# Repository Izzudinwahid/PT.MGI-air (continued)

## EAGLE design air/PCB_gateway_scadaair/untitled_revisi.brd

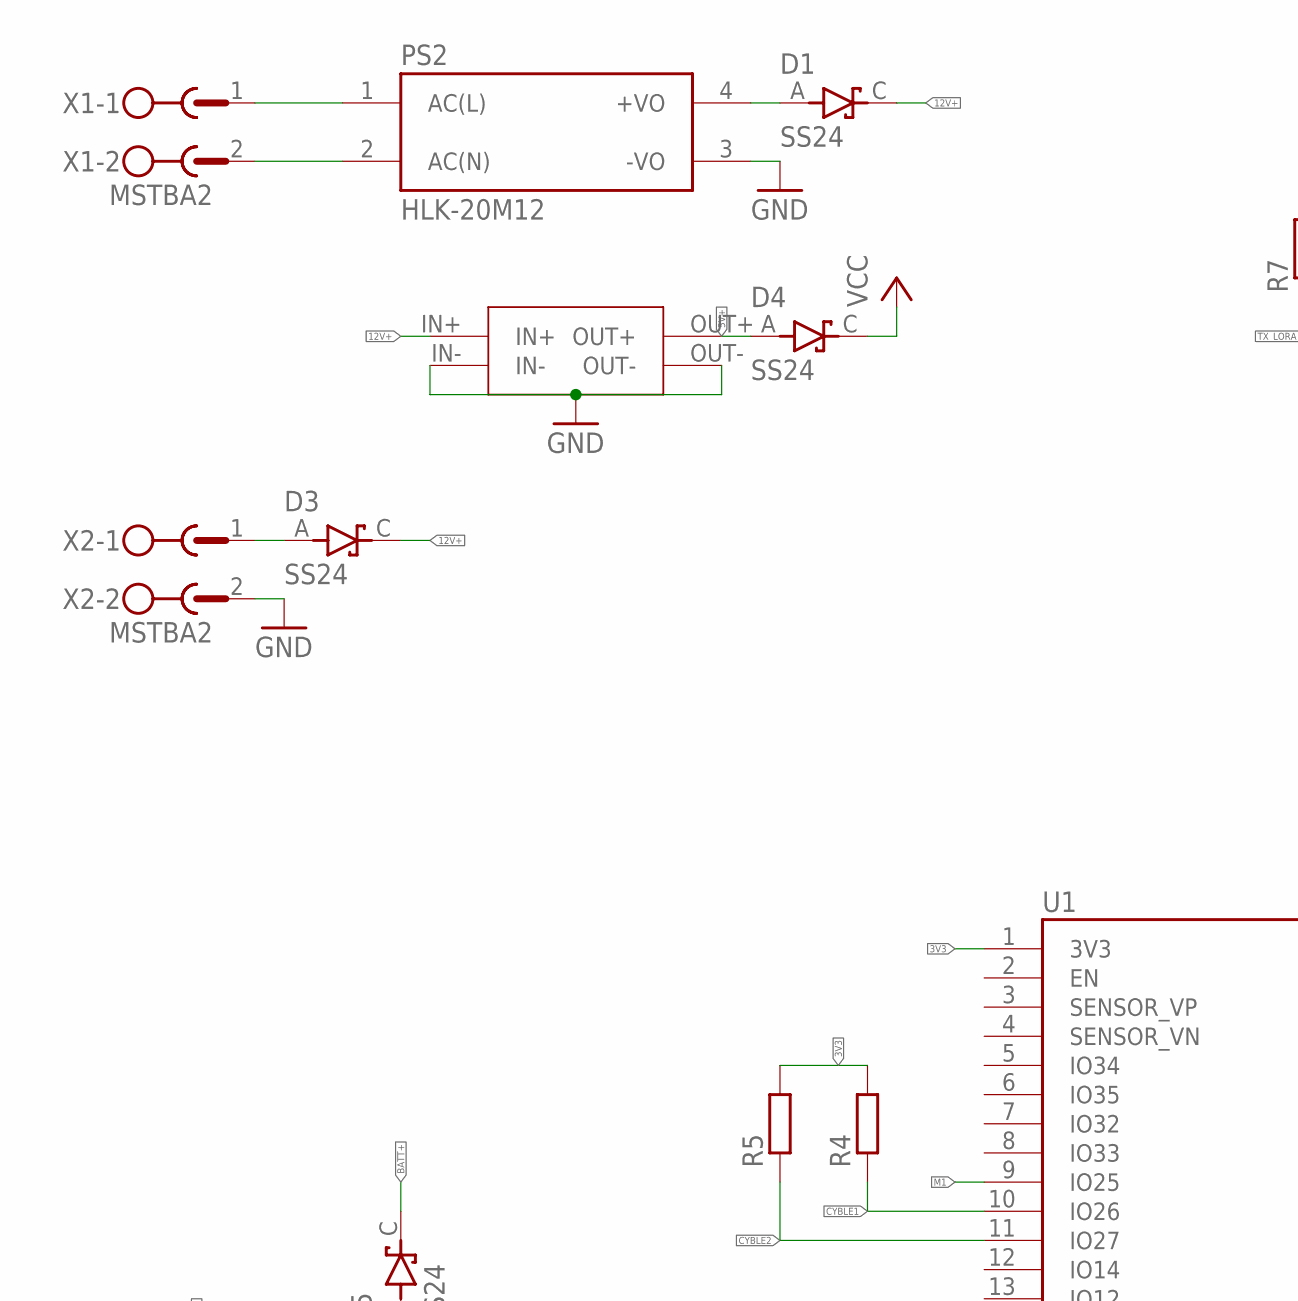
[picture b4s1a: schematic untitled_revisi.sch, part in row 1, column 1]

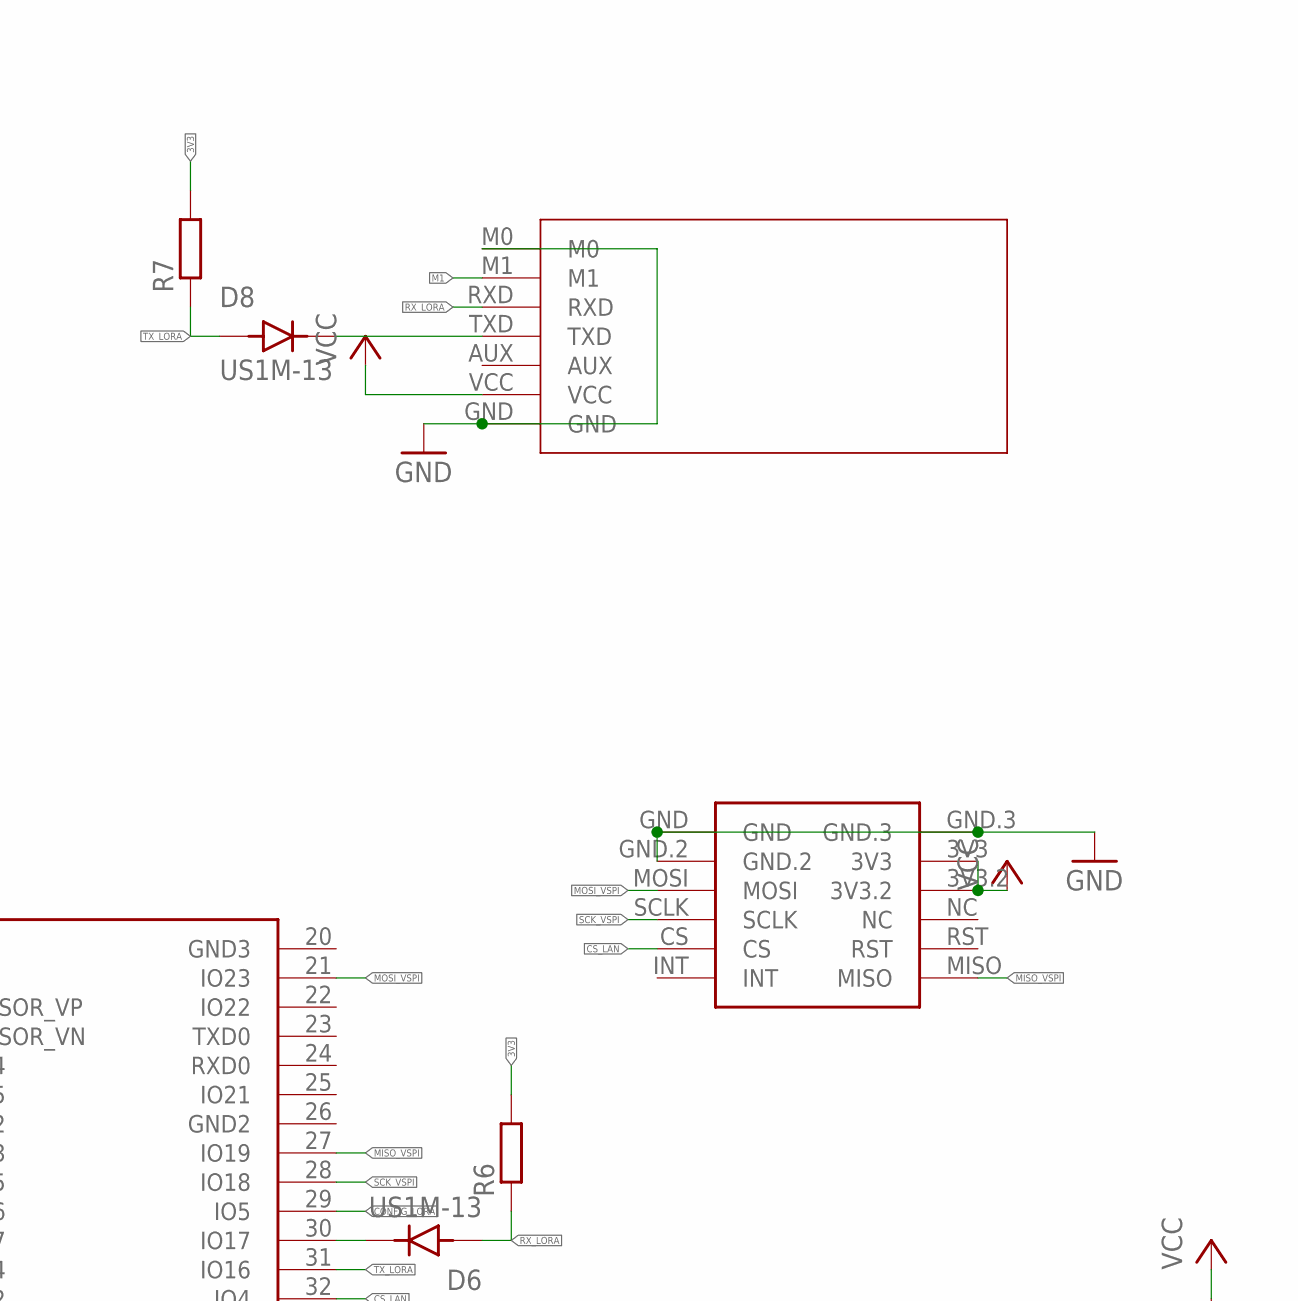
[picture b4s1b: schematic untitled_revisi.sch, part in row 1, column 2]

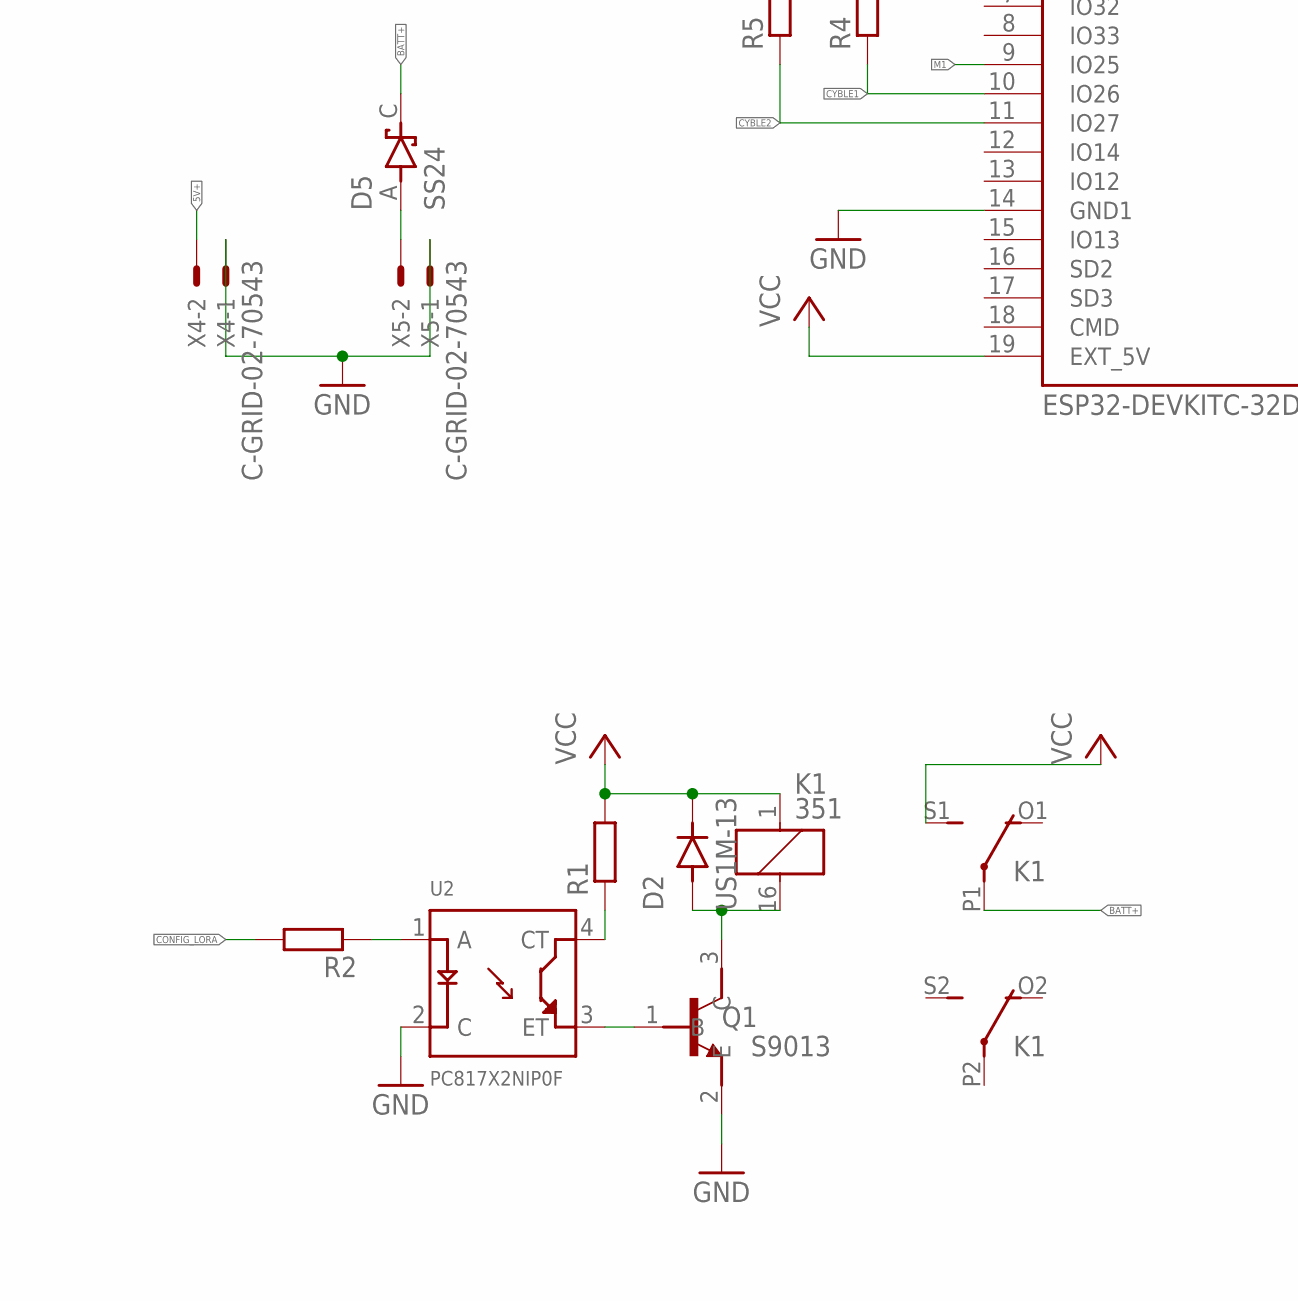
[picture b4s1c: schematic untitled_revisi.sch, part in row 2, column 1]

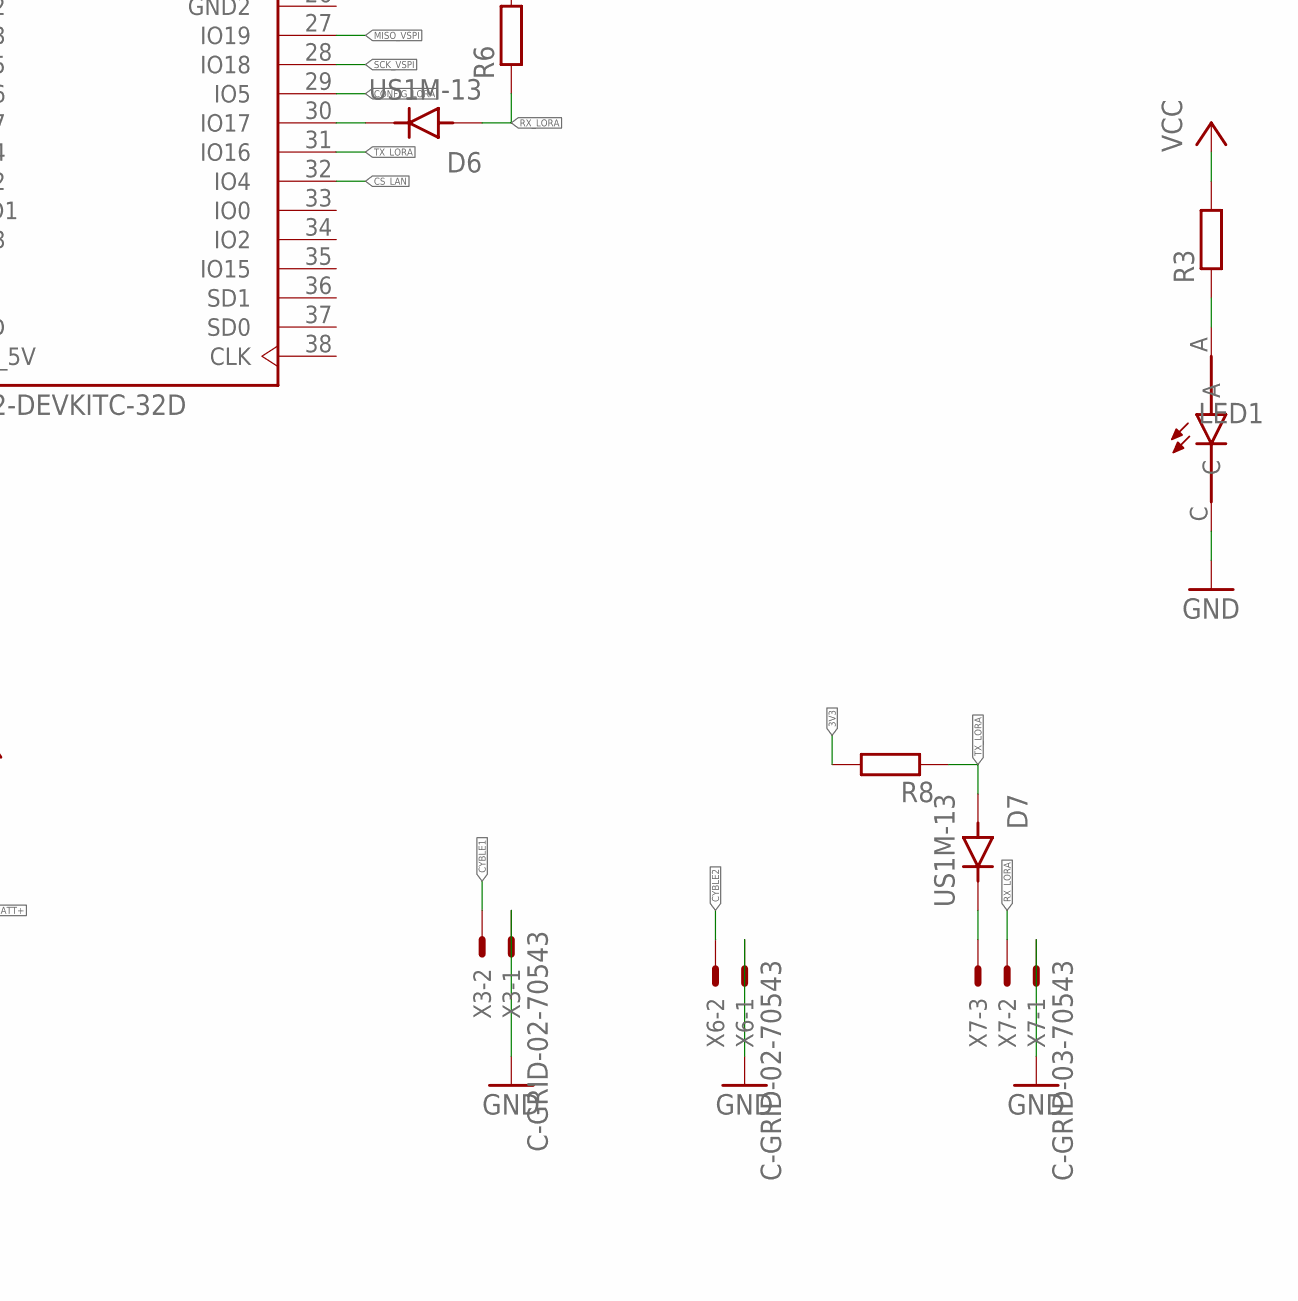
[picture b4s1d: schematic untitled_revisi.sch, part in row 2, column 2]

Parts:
D1, D3, D4, D5: SS24; DIOM5336X265N
D2, D6, D7, D8: US1M-13; DIOM5226X240N
EBYTEE220-900T22D1: EBYTEE220-900T22D
K1: 351
LED1: SML-LXT0805IW-TR; LEDC2012X120N
MINI1: MINI560
PS2: HLK-20M12; CONV_HLK-20M12
Q1: S9013; SOT95P240X120-3N
R1, R2, R3, R4, R5, R6, R7, R8: R-EU_R0805; R0805
U1: ESP32-DEVKITC-32D; MODULE_ESP32-DEVKITC-32D
U2: PC817X2NIP0F; SOT254P975X400-4N
U$1: MINI_W5500
X1, X2: MSTBA2
X3, X4, X5, X6: C-GRID-02-70543; 70543-02
X7: C-GRID-03-70543; 70543-03

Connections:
3V3: R4.2, R5.2, R6.2, R7.2, R8.2, U1.1 (3V3)
5V+: D4.A, MINI1.OUT+, X4.2
12V+: D1.C (K), D3.C (K), MINI1.IN+
BATT+: D5.C (K), K1.P1
CONFIG_LORA: R2.2, U1.29 (IO5)
CS_LAN: U1.32 (IO4), U$1.CS
CYBLE1: R4.1, U1.10 (IO26), X3.2
CYBLE2: R5.1, U1.11 (IO27), X6.2
GND: EBYTEE220-900T22D1.GND, EBYTEE220-900T22D1.M0, LED1.C, MINI1.IN-, MINI1.OUT-, PS2.3 (-VO), Q1.2 (E), U1.14 (GND1), U2.2 (C), U$1.GND, U$1.GND.2, U$1.GND.3, X2.2, X3.1, X4.1, X5.1, X6.1, X7.1
GND2: U1.26 (GND2)
GND3: U1.20 (GND3)
M1: EBYTEE220-900T22D1.M1, U1.9 (IO25)
MISO_VSPI: U1.27 (IO19), U$1.MISO
MOSI_VSPI: U1.21 (IO23), U$1.MOSI
unnamed: PS2.1 (AC(L)), X1.1
unnamed: PS2.2 (AC(N)), X1.2
unnamed: D1.A, PS2.4 (+VO)
unnamed: R2.1, U2.1 (A)
unnamed: D3.A, X2.1
unnamed: D2.A, K1.16 (2), Q1.3 (C)
unnamed: Q1.1 (B), U2.3 (ET)
unnamed: R1.1, U2.4 (CT)
unnamed: D6.C (K), U1.30 (IO17)
unnamed: LED1.A, R3.1
unnamed: D8.C (K), EBYTEE220-900T22D1.TXD
unnamed: D5.A, X5.2
unnamed: D7.C (K), X7.3
RX_LORA: D6.A, EBYTEE220-900T22D1.RXD, R6.1, X7.2
SCK_VSPI: U1.28 (IO18), U$1.SCLK
TX_LORA: D7.A, D8.A, R7.1, R8.1, U1.31 (IO16)
VCC: D2.C (K), D4.C (K), EBYTEE220-900T22D1.VCC, K1.1, K1.S1 (S), R1.2, R3.2, U1.19 (EXT_5V), U$1.3V3, U$1.3V3.2

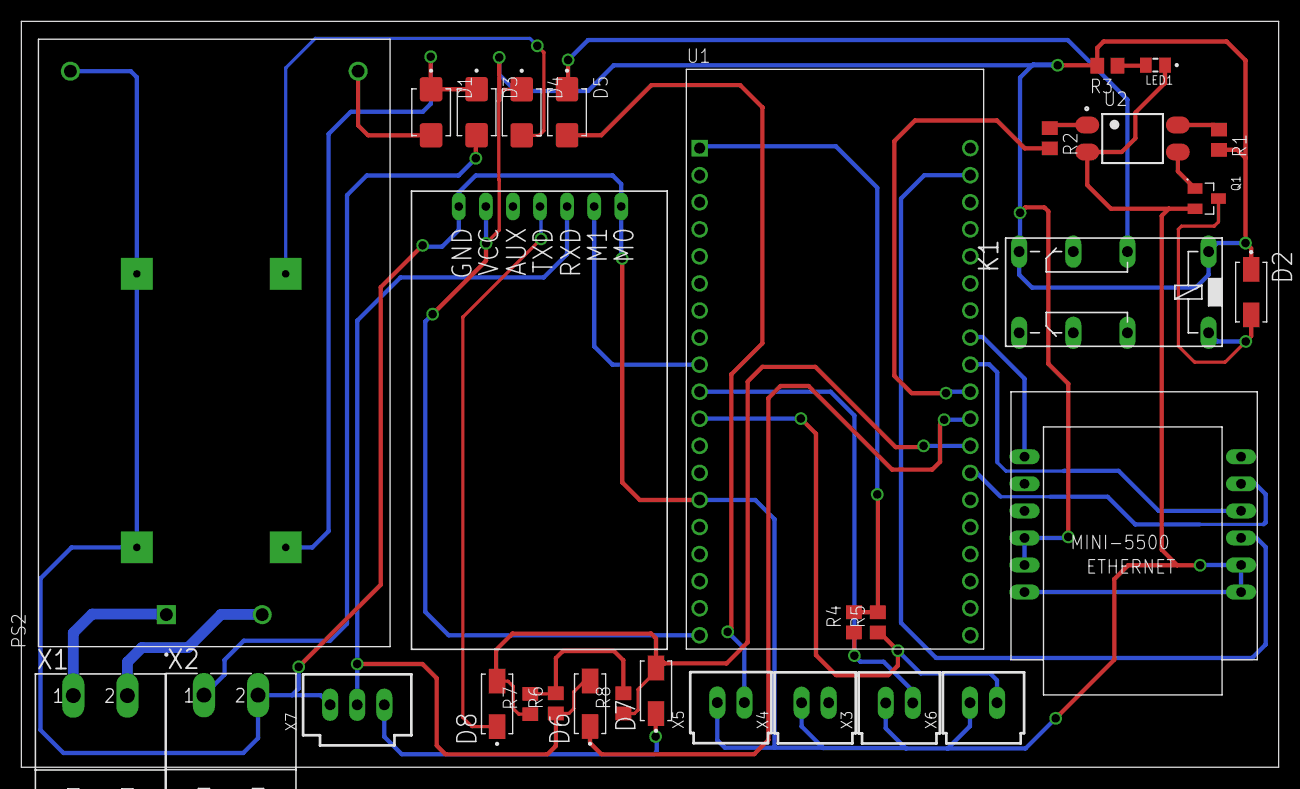
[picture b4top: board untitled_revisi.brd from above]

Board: 2 copper layers, 118.0 x 70.0 mm, 32 parts (1 on the bottom side), 29 nets.

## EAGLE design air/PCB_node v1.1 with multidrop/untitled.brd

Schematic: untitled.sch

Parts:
ADS1, ADS2: ADS1115
BT1: ML414H_IV01E; SEIKO_ML414H_IV01E
C1, C7, C8, C9, C14, C19, C20, C24: 1uF; C0805K
C2, C6, C15: 10uF/16V; 153CLV-0505
C3, C10, C11, C16, C17, C18, C21: 100nF; C0805K
C4, C5, C12, C13: 22pF; C0805K
C22: 27nH; C0805K
C23: 10nF; C0805K
D1, D2, D7, D8, D17: 1N5819HW-7; SOD3715X145N
D3, D9, D10, D11, D12, D16: SML-LXT0805IW-TR; LEDC2012X120N
D4, D5, D6, D13, D14, D15, D18: US1M-13; DIOM5226X240N
EBYTEE220-900T22D1: EBYTEE220-900T22D
J1, J2: 10118193-0001LF; FCI_10118193-0001LF
J3: U.FL-R-SMT(01); HRS_U.FL-R-SMT(01)
K1, K2, K4, K5: 351
K3: SRD-05VDC-SL-C; RELAY_SRD-05VDC-SL-C
NEO-6MGPS1: NEO-6MGPS
Q1, Q2, Q8, Q9: MMBT3904; SOT95P240X120-3N
Q3, Q7: 12MHz; SM49
Q4, Q5, Q6, Q10, Q11, Q12: S9013; SOT95P240X120-3N
R1, R2, R4, R5, R12, R14, R17, R18, R19, R20, R24, R25, R26, R27, R28, R29, R31, R35, R37: 10k; M0805
R3, R11, R13, R22, R23, R33, R34, R36: 1k; M0805
R6, R7, R8, R10, R30: 560; M0805
R9, R15, R16, R21: R-EU_0207/12; 0207/12
R32: 10; M0805
S1, S2, S3, S4: TL1015AF160QG; SW_TL1015AF160QG
SJ1, SJ2, SJ3: SJ
SUPER-STEPDOWN1: SUPER-STEPDOWN
SV1: FE09-1; FE09
U1, U7: CH340G; SOIC127P600X180-16N
U2, U9: ESP32-WROOM-32D; MODULE_ESP32-WROOM-32D
U3, U8: AMS1117; SOT229P700X180-4N
U4, U5, U6, U11, U13: PC817X2NIP0F; SOT254P975X400-4N
U10: ADS1115IDGSR; SOP50P490X110-10N
U12: NEO-M8N-0; XCVR_NEO-M8N-0
X1, X2, X5, X8: MSTBA2
X3, X6: MSTBA4
X4: MSTBA3
X7: C-GRID-02-70543; 70543-02

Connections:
24V+: R15.2, SUPER-STEPDOWN1.IN+, X1.1
A0: ADS1.A0, ADS2.A0, R15.1, R16.2, U10.4 (AIN0)
A1: ADS1.A1
A2: ADS1.A2
A3: ADS1.A3
BACKUP: BT1.1 (POS), C24.1, R34.1, U12.22 (V_BCKP)
CONFIG_LORA: R11.2, U9.10 (IO25)
CYBLE1: R6.1, U2.10 (IO25), X3.1
CYBLE2: R7.1, U2.11 (IO26), X3.2
CYBLE3: R8.1, R9.1, R21.2, U2.12 (IO27)
CYBLE4: R23.2, U2.8 (IO32)
CYBLE5: R10.1, U2.9 (IO33), X3.4
DTR: Q2.2 (E), R1.1, U1.13 (!DTR)
DTR1: Q9.2 (E), R25.1, U7.13 (!DTR)
D_SEL: R35.1, SJ1.2, U12.2 (D_SEL)
EN: C10.1, Q1.3 (C), R4.1, S1.1, U2.3 (EN)
EN1: C17.1, Q8.3 (C), R27.1, S3.1, U9.3 (EN)
GND: ADS1.ADDR, ADS1.GND, ADS2.ADDR, ADS2.GND, BT1.2 (NEG), C1.2, C2.-, C3.2, C4.1, C5.1, C6.-, C7.2, C8.2, C9.2, C10.2, C11.2, C12.1, C13.1, C14.2, C15.-, C16.2, C17.2, C18.2, C19.2, C20.2, C21.2, C23.2, C24.2, D3.C, EBYTEE220-900T22D1.GND, EBYTEE220-900T22D1.M0, J1.5 (GND), J1.S1 (SHIELD), J1.S2 (SHIELD), J1.S3 (SHIELD), J1.S4 (SHIELD), J1.S5 (SHIELD), J1.S6 (SHIELD), J2.5 (GND), J2.S1 (SHIELD), J2.S2 (SHIELD), J2.S3 (SHIELD), J2.S4 (SHIELD), J2.S5 (SHIELD), J2.S6 (SHIELD), J3.1 (GND), J3.2 (GND), K3.COM, NEO-6MGPS1.GND, Q4.2 (E), Q5.2 (E), Q6.2 (E), Q10.2 (E), Q11.2 (E), Q12.2 (E), R16.1, R21.1, S1.2, S2.2, S3.2, S4.2, SJ1.1, SUPER-STEPDOWN1.GND, SUPER-STEPDOWN1.IN-, U1.1 (GND), U2.1 (GND), U2.15 (GND), U2.38 (GND), U2.39_1 (GND), U2.39_2 (GND), U2.39_3 (GND), U2.39_4 (GND), U2.39_5 (GND), U2.39_6 (GND), U2.39_7 (GND), U2.39_8 (GND), U2.39_9 (GND), U2.39_10 (GND), U2.39_11 (GND), U2.39_12 (GND), U2.39_13 (GND), U2.39_14 (GND), U2.39_15 (GND), U2.39_16 (GND), U2.39_17 (GND), U2.39_18 (GND), U2.39_19 (GND), U2.39_20 (GND), U2.39_21 (GND), U3.1 (ADJ/GND), U4.2 (C), U5.2 (C), U6.2 (C), U7.1 (GND), U8.1 (ADJ/GND), U9.1 (GND), U9.15 (GND), U9.38 (GND), U9.39_1 (GND), U9.39_2 (GND), U9.39_3 (GND), U9.39_4 (GND), U9.39_5 (GND), U9.39_6 (GND), U9.39_7 (GND), U9.39_8 (GND), U9.39_9 (GND), U9.39_10 (GND), U9.39_11 (GND), U9.39_12 (GND), U9.39_13 (GND), U9.39_14 (GND), U9.39_15 (GND), U9.39_16 (GND), U9.39_17 (GND), U9.39_18 (GND), U9.39_19 (GND), U9.39_20 (GND), U9.39_21 (GND), U10.1 (ADDR), U10.3 (GND), U11.2 (C), U12.10 (GND), U12.12 (GND), U12.13 (GND), U12.24 (GND), U13.2 (C), X2.2, X4.3, X6.4, X7.1
GND-BATT: K3.NO, X1.2, X2.1
IO0: C11.1, Q2.3 (C), R5.1, S2.1, U2.25 (IO0)
IO01: C18.1, Q9.3 (C), R28.1, S4.1, U9.25 (IO0)
M1: EBYTEE220-900T22D1.M1, U9.29 (IO5)
M2_BATT-BACK-SWITCH: R36.2, U9.24 (IO2)
M2_RX: D14.A, K4.P2, R30.2
M2_SWITCHGPS: R22.2, U9.11 (IO26)
M2_TX: K4.P1, U9.27 (IO16)
unnamed: C4.2, Q3.2, U1.7 (XI)
unnamed: C5.2, Q3.1, U1.8 (XO)
unnamed: Q1.1 (B), R1.2
unnamed: Q8.1 (B), R25.2
unnamed: C3.1, U1.4 (V3)
unnamed: D3.A, R3.1
unnamed: D1.A, SUPER-STEPDOWN1.+5V
unnamed: Q2.1 (B), R2.2
unnamed: R11.1, U4.1 (A)
unnamed: R12.2, U4.4 (CT)
unnamed: R13.1, U5.1 (A)
unnamed: D4.A, K1.16 (2), Q4.3 (C)
unnamed: Q4.1 (B), U4.3 (ET)
unnamed: R14.2, U5.4 (CT)
unnamed: D5.A, K2.16 (2), Q5.3 (C)
unnamed: Q9.1 (B), R26.2
unnamed: Q5.1 (B), U5.3 (ET)
unnamed: D9.A, R17.1
unnamed: R24.2, U6.4 (CT)
unnamed: D6.A, K3.A2, Q6.3 (C)
unnamed: D10.A, R18.1
unnamed: D11.A, R19.1
unnamed: D12.A, R20.1
unnamed: Q6.1 (B), U6.3 (ET)
unnamed: R23.1, U6.1 (A)
unnamed: C16.1, U7.4 (V3)
unnamed: C13.2, Q7.1, U7.8 (XO)
unnamed: C12.2, Q7.2, U7.7 (XI)
unnamed: R36.1, U13.1 (A)
unnamed: R22.1, U11.1 (A)
unnamed: Q10.1 (B), U11.3 (ET)
unnamed: R29.2, U11.4 (CT)
unnamed: D13.A, K4.16 (2), Q10.3 (C)
unnamed: D14.C (K), U9.28 (IO17)
unnamed: D15.C (K), U2.28 (IO17)
unnamed: C22.1, C23.1, R32.2
unnamed: R32.1, U12.9 (VCC_RF)
unnamed: D16.C, Q12.3 (C)
unnamed: D16.A, R33.1
unnamed: R37.2, U13.4 (CT)
unnamed: D17.C (K), R34.2
unnamed: D18.A, K5.16 (2), Q11.3 (C)
unnamed: Q11.1 (B), U13.3 (ET)
unnamed: K5.S1 (S), X7.2
OUT1: SV1.1, U9.37 (IO23)
OUT2: SV1.2, U9.26 (IO4)
OUT3: SV1.3, U9.23 (IO15)
OUT4: SV1.4, U9.16 (IO13)
OUT5: SV1.5, U9.14 (IO12)
OUT6: SV1.6, U9.13 (IO14)
OUT7: SV1.7, U9.12 (IO27)
OUT8: SV1.8, U9.9 (IO33)
OUT9: SV1.9, U9.8 (IO32)
OUT+: ADS1.VDD, ADS2.VDD, C6.+, C7.1, C8.1, C19.1, C21.1, D1.C (K), D2.C (K), D4.C (K), D5.C (K), D6.C (K), D7.C (K), D8.C (K), D13.C (K), D18.C (K), EBYTEE220-900T22D1.VCC, K1.1, K2.1, K3.A1, K4.1, K5.1, NEO-6MGPS1.5V, R3.2, R12.1, R14.1, R24.1, R29.1, R37.1, U3.3 (VIN), U8.3 (VIN), U10.8 (VDD), X6.1
OUT-BATT: D8.A, K5.P1
PB-PWR: R9.2, X3.3
RF_IN: C22.2, J3.3 (SIG), U12.11 (RF_IN)
RTS: Q1.2 (E), R2.1, U1.14 (!RTS)
RTS1: Q8.2 (E), R26.1, U7.14 (!RTS)
RX: D10.C, U1.3 (RXD), U2.35 (TXD0)
RX1: D12.C, U7.3 (RXD), U9.35 (TXD0)
RXLORA_CONFIG: K1.S1 (S), X4.2
RXLORA_MICRO: D15.A, K1.O1 (O), R31.1
RX_GPS: NEO-6MGPS1.RX, SJ2.2, U12.21 (RXD/SPI_MOSI)
RX_GPS1: K4.O2 (O), SJ2.1
RX_LORA: EBYTEE220-900T22D1.RXD, K1.P1, K4.S2 (S)
RX_MICRO: U2.13 (IO14), U9.30 (IO18)
SCL: ADS1.SCL, U2.36 (IO22), U10.10 (SCL), X6.3
SCL1: ADS2.SCL, U9.36 (IO22), X8.1
SDA: ADS1.SDA, U2.33 (IO21), U10.9 (SDA), X6.2
SDA1: ADS2.SDA, U9.33 (IO21), X8.2
TIMEPULSE: Q12.1 (B), U12.3 (TIMEPULSE)
TX: D9.C, U1.2 (TXD), U2.34 (RXD0)
TX1: D11.C, U7.2 (TXD), U9.34 (RXD0)
TXLORA_CONFIG: K1.S2 (S), X4.1
TXLORA_MICRO: K1.O2 (O), U2.27 (IO16)
TX_GPS: NEO-6MGPS1.TX, SJ3.2, U12.20 (TXD/SPI_MISO)
TX_GPS1: K4.O1 (O), SJ3.1
TX_LORA: EBYTEE220-900T22D1.TXD, K1.P2, K4.S1 (S)
TX_MICRO: U2.23 (IO15), U9.31 (IO19)
USB1_N: J2.2 (D-), U7.6 (UD-)
USB1_P: J2.3 (D+), U7.5 (UD+)
USB_N: J1.2 (D-), U1.6 (UD-)
USB_P: J1.3 (D+), U1.5 (UD+)
VALVE: R13.2, U2.37 (IO23)
VALVE1: K2.S1 (S), X5.2
VALVE2: K2.P1, X5.1
VCC: C9.1, R4.2, R5.2, R6.2, R7.2, R8.2, R10.2, R17.2, R18.2, R31.2, U2.2 (3V3), U3.2 (VOUT), U3.4 (VOUT)
VCC1: C20.1, D17.A, R19.2, R20.2, R27.2, R28.2, R30.1, R33.2, R35.2, U8.2 (VOUT), U8.4 (VOUT), U9.2 (3V3), U12.23 (VCC)
VDD_USB: U12.7 (VDD_USB)
VUSB: C1.1, C2.+, D2.A, J1.1 (VUSB), U1.16 (VCC)
VUSB1: C14.1, C15.+, D7.A, J2.1 (VUSB), U7.16 (VCC)

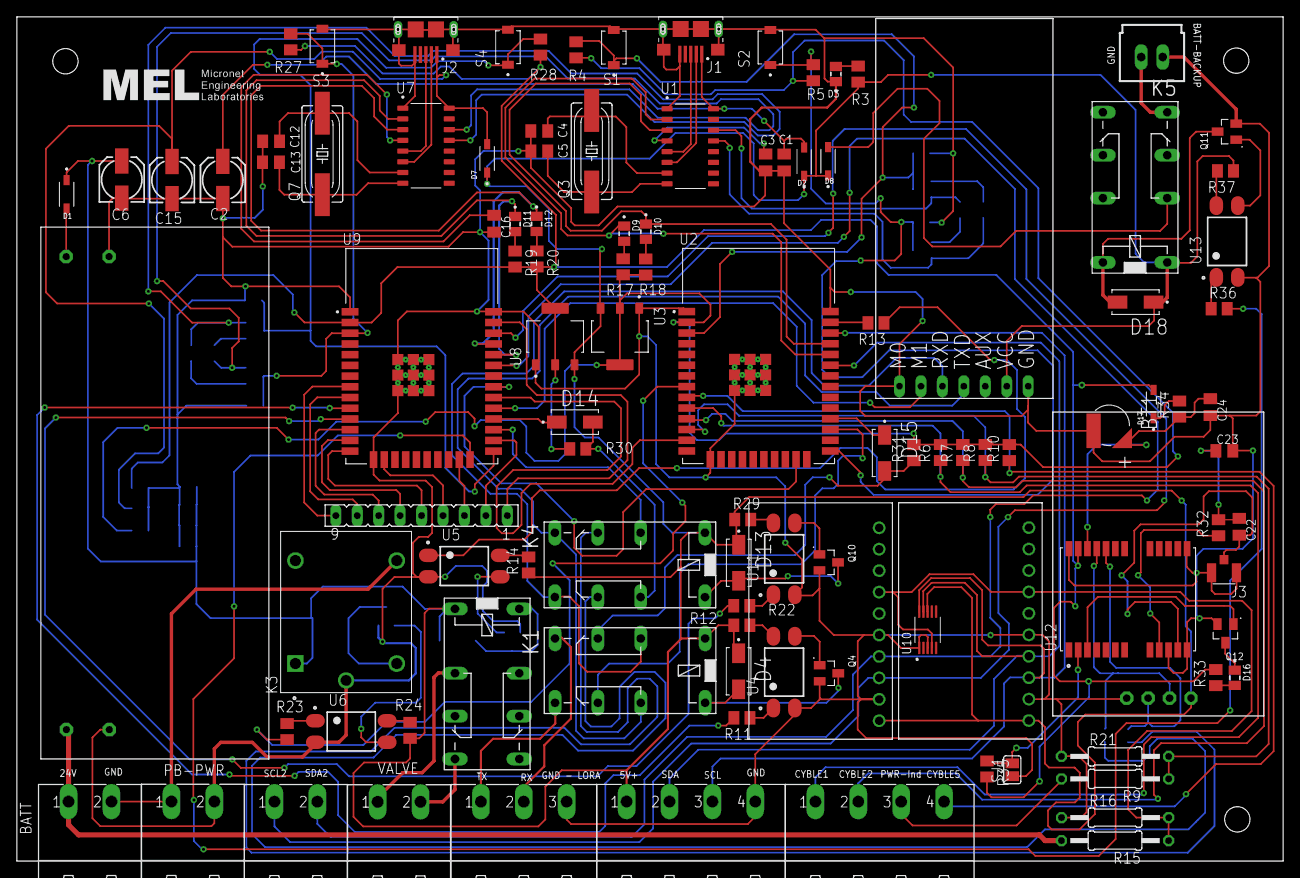
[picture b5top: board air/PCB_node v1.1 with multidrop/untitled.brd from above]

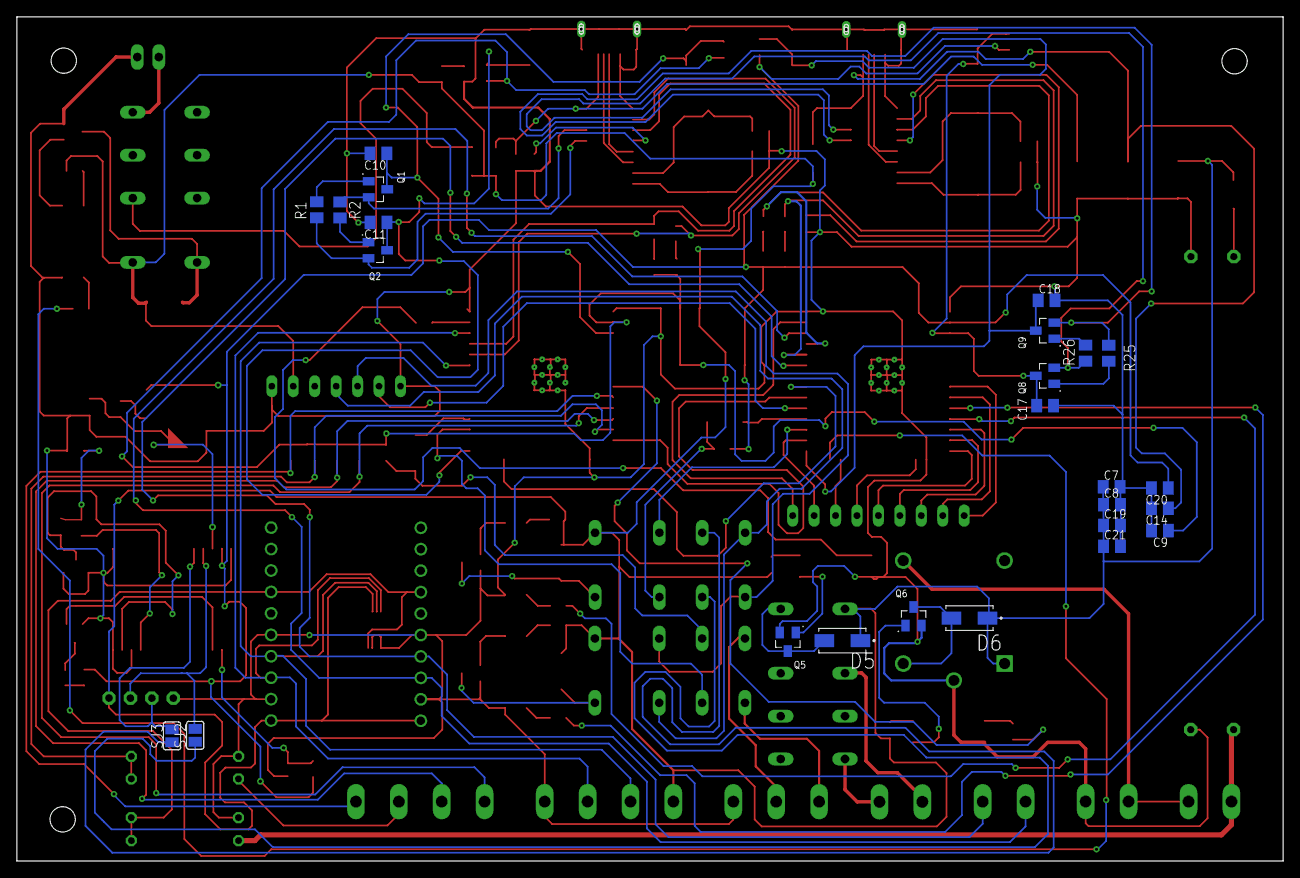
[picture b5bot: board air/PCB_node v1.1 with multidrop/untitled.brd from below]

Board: 2 copper layers, 150.0 x 100.0 mm, 134 parts (25 on the bottom side), 114 nets.
